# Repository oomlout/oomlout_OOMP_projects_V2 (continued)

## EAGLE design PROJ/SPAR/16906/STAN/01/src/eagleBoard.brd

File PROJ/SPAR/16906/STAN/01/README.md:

Contents
========

* [PRPR16906 > Qwiic Multi Port Board](#prpr16906--qwiic-multi-port-board)
	* [OOMP Parts](#oomp-parts)
	* [Images](#images)
	* [Tags](#tags)
  
![][im]
# PRPR16906 > Qwiic Multi Port Board

- ID: PROJ-SPAR-16906-STAN-01
- Hex ID: PRPR16906
- Name: Qwiic Multi Port Board
- Path: oomlout_OOMP_projects_V2/PROJ/SPAR/16906/STAN/01/
- Description: Qwiic Multi Port Board
- Long Link: [http://oom.lt/PROJ-SPAR-16906-STAN-01](http://oom.lt/PROJ-SPAR-16906-STAN-01)
- Short Link: [http://oom.lt/PRPR16906](http://oom.lt/PRPR16906)

## OOMP Parts

|Image|OOMP ID|Designators|
| :--- | :--- | :--- |
||[HEAD-JSTSH-X-PI04-RS](https://github.com/oomlout/oomlout_OOMP_parts_V2/tree/main/HEAD/JSTSH/X/PI04/RS/)|[J4,J3,J2,J1](https://github.com/oomlout/oomlout_OOMP_parts_V2/tree/main/HEAD/JSTSH/X/PI04/RS/)|
||||

## Images

|kicadPcb3dFront<br>|kicadPcb3dBack<br>|kicadPcb3d<br>|pcbdraw<br>|
| :---: | :---: | :---: | :---: |
|pcbdrawBack<br>||||

## Tags

|Tag Name|Tag Code|Tag Value|
| :--- | :--- | :--- |
|OOMP Type|oompType|PROJ|
|OOMP Size|oompSize|SPAR|
|OOMP Color|oompColor|16906|
|OOMP Description|oompDesc|STAN|
|OOMP Index|oompIndex|01|
|Full OOMP ID|oompID|PROJ-SPAR-16906-STAN-01|
|Hex ID (short code)|hexID|PRPR16906|
|name|name|Qwiic Multi Port Board|
|gitRepo|gitRepo|https://github.com/sparkfun/Qwiic_Multi_Port_Board|
|gitName|gitName|Qwiic_Multi_Port_Board|
|eagleBoard|eagleBoard|/Qwiic_Multi_Port_Board/Qwiic_Multi_Port_Board.brd|
|eagleSchem|eagleSchem|/Qwiic_Multi_Port_Board/Qwiic_Multi_Port_Board.sch|
|OOMP Parts List|oompParts|<table><tr><td>'J4'</td></tr><tr><td> <table><tr><td>'OOMPID'</td></tr><tr><td> 'HEAD-JSTSH-X-PI04-RS'</td><td> 'FULL'</td></tr><tr><td> <table><tr><td>'DESC'</td></tr><tr><td> ''</td><td> 'PART'</td></tr><tr><td> 'J4'</td><td> 'DEVICE'</td></tr><tr><td> 'JST04_1MM_RA QWIIC_RIGHT_ANGLE'</td><td> 'PACKAGE'</td></tr><tr><td> 'JST04_1MM_RA'</td><td> 'PARTLETTER'</td></tr><tr><td> 'J'</td><td> 'VALUE'</td></tr><tr><td> 'QWIIC_RIGHT_ANGLE'</td><td> 'VALUENUMBER'</td></tr><tr><td> '__'</td><td> 'PACKAGENUMBER'</td></tr><tr><td> '041'</td><td> 'BOM'</td></tr><tr><td> ''</td><td> 'OWNER'</td></tr><tr><td> 'SPAR'</td><td> 'FULL'</td></tr><tr><td> 'J4</td><td>QWIIC_RIGHT_ANGLE</td><td>JST04_1MM_RA QWIIC_RIGHT_ANGLE</td><td>JST04_1MM_RA</td><td></td><td></td><td>'</td></tr></table></td></tr></table></td><td> 'J3'</td></tr><tr><td> <table><tr><td>'OOMPID'</td></tr><tr><td> 'HEAD-JSTSH-X-PI04-RS'</td><td> 'FULL'</td></tr><tr><td> <table><tr><td>'DESC'</td></tr><tr><td> ''</td><td> 'PART'</td></tr><tr><td> 'J3'</td><td> 'DEVICE'</td></tr><tr><td> 'JST04_1MM_RA QWIIC_RIGHT_ANGLE'</td><td> 'PACKAGE'</td></tr><tr><td> 'JST04_1MM_RA'</td><td> 'PARTLETTER'</td></tr><tr><td> 'J'</td><td> 'VALUE'</td></tr><tr><td> 'QWIIC_RIGHT_ANGLE'</td><td> 'VALUENUMBER'</td></tr><tr><td> '__'</td><td> 'PACKAGENUMBER'</td></tr><tr><td> '041'</td><td> 'BOM'</td></tr><tr><td> ''</td><td> 'OWNER'</td></tr><tr><td> 'SPAR'</td><td> 'FULL'</td></tr><tr><td> 'J3</td><td>QWIIC_RIGHT_ANGLE</td><td>JST04_1MM_RA QWIIC_RIGHT_ANGLE</td><td>JST04_1MM_RA</td><td></td><td></td><td>'</td></tr></table></td></tr></table></td><td> 'J2'</td></tr><tr><td> <table><tr><td>'OOMPID'</td></tr><tr><td> 'HEAD-JSTSH-X-PI04-RS'</td><td> 'FULL'</td></tr><tr><td> <table><tr><td>'DESC'</td></tr><tr><td> ''</td><td> 'PART'</td></tr><tr><td> 'J2'</td><td> 'DEVICE'</td></tr><tr><td> 'JST04_1MM_RA QWIIC_RIGHT_ANGLE'</td><td> 'PACKAGE'</td></tr><tr><td> 'JST04_1MM_RA'</td><td> 'PARTLETTER'</td></tr><tr><td> 'J'</td><td> 'VALUE'</td></tr><tr><td> 'QWIIC_RIGHT_ANGLE'</td><td> 'VALUENUMBER'</td></tr><tr><td> '__'</td><td> 'PACKAGENUMBER'</td></tr><tr><td> '041'</td><td> 'BOM'</td></tr><tr><td> ''</td><td> 'OWNER'</td></tr><tr><td> 'SPAR'</td><td> 'FULL'</td></tr><tr><td> 'J2</td><td>QWIIC_RIGHT_ANGLE</td><td>JST04_1MM_RA QWIIC_RIGHT_ANGLE</td><td>JST04_1MM_RA</td><td></td><td></td><td>'</td></tr></table></td></tr></table></td><td> 'J1'</td></tr><tr><td> <table><tr><td>'OOMPID'</td></tr><tr><td> 'HEAD-JSTSH-X-PI04-RS'</td><td> 'FULL'</td></tr><tr><td> <table><tr><td>'DESC'</td></tr><tr><td> ''</td><td> 'PART'</td></tr><tr><td> 'J1'</td><td> 'DEVICE'</td></tr><tr><td> 'JST04_1MM_RA QWIIC_RIGHT_ANGLE'</td><td> 'PACKAGE'</td></tr><tr><td> 'JST04_1MM_RA'</td><td> 'PARTLETTER'</td></tr><tr><td> 'J'</td><td> 'VALUE'</td></tr><tr><td> 'QWIIC_RIGHT_ANGLE'</td><td> 'VALUENUMBER'</td></tr><tr><td> '__'</td><td> 'PACKAGENUMBER'</td></tr><tr><td> '041'</td><td> 'BOM'</td></tr><tr><td> ''</td><td> 'OWNER'</td></tr><tr><td> 'SPAR'</td><td> 'FULL'</td></tr><tr><td> 'J1</td><td>QWIIC_RIGHT_ANGLE</td><td>JST04_1MM_RA QWIIC_RIGHT_ANGLE</td><td>JST04_1MM_RA</td><td></td><td></td><td>'</td></tr></table></td></tr></table></td></tr></table>|
|Parts as pulled from a BOM|rawParts|<table><tr><td>'kicadBom'</td></tr><tr><td> [<table><tr><td>'Part'</td></tr><tr><td> 'U$4'</td><td> 'Value'</td></tr><tr><td> ''</td><td> 'Device'</td></tr><tr><td> 'MULTI1 '</td><td> 'Package'</td></tr><tr><td> 'MULTI1'</td><td> 'Description'</td></tr><tr><td> ''</td><td> 'BOM'</td></tr><tr><td> ''</td></tr></table></td><td> <table><tr><td>'Part'</td></tr><tr><td> 'U$7'</td><td> 'Value'</td></tr><tr><td> ''</td><td> 'Device'</td></tr><tr><td> 'MULTI1 '</td><td> 'Package'</td></tr><tr><td> 'MULTI1'</td><td> 'Description'</td></tr><tr><td> ''</td><td> 'BOM'</td></tr><tr><td> ''</td></tr></table></td><td> <table><tr><td>'Part'</td></tr><tr><td> 'J4'</td><td> 'Value'</td></tr><tr><td> 'QWIIC_RIGHT_ANGLE'</td><td> 'Device'</td></tr><tr><td> 'JST04_1MM_RA QWIIC_RIGHT_ANGLE'</td><td> 'Package'</td></tr><tr><td> 'JST04_1MM_RA'</td><td> 'Description'</td></tr><tr><td> ''</td><td> 'BOM'</td></tr><tr><td> ''</td></tr></table></td><td> <table><tr><td>'Part'</td></tr><tr><td> 'J3'</td><td> 'Value'</td></tr><tr><td> 'QWIIC_RIGHT_ANGLE'</td><td> 'Device'</td></tr><tr><td> 'JST04_1MM_RA QWIIC_RIGHT_ANGLE'</td><td> 'Package'</td></tr><tr><td> 'JST04_1MM_RA'</td><td> 'Description'</td></tr><tr><td> ''</td><td> 'BOM'</td></tr><tr><td> ''</td></tr></table></td><td> <table><tr><td>'Part'</td></tr><tr><td> 'J2'</td><td> 'Value'</td></tr><tr><td> 'QWIIC_RIGHT_ANGLE'</td><td> 'Device'</td></tr><tr><td> 'JST04_1MM_RA QWIIC_RIGHT_ANGLE'</td><td> 'Package'</td></tr><tr><td> 'JST04_1MM_RA'</td><td> 'Description'</td></tr><tr><td> ''</td><td> 'BOM'</td></tr><tr><td> ''</td></tr></table></td><td> <table><tr><td>'Part'</td></tr><tr><td> 'J1'</td><td> 'Value'</td></tr><tr><td> 'QWIIC_RIGHT_ANGLE'</td><td> 'Device'</td></tr><tr><td> 'JST04_1MM_RA QWIIC_RIGHT_ANGLE'</td><td> 'Package'</td></tr><tr><td> 'JST04_1MM_RA'</td><td> 'Description'</td></tr><tr><td> ''</td><td> 'BOM'</td></tr><tr><td> ''</td></tr></table></td><td> <table><tr><td>'Part'</td></tr><tr><td> 'FRAME1'</td><td> 'Value'</td></tr><tr><td> 'FRAME-LETTER'</td><td> 'Device'</td></tr><tr><td> 'CREATIVE_COMMONS FRAME-LETTER'</td><td> 'Package'</td></tr><tr><td> 'CREATIVE_COMMONS'</td><td> 'Description'</td></tr><tr><td> ''</td><td> 'BOM'</td></tr><tr><td> ''</td></tr></table></td><td> <table><tr><td>'Part'</td></tr><tr><td> 'H1'</td><td> 'Value'</td></tr><tr><td> 'STAND-OFFTIGHT'</td><td> 'Device'</td></tr><tr><td> 'STAND-OFF-TIGHT STAND-OFFTIGHT'</td><td> 'Package'</td></tr><tr><td> 'STAND-OFF-TIGHT'</td><td> 'Description'</td></tr><tr><td> ''</td><td> 'BOM'</td></tr><tr><td> ''</td></tr></table></td><td> <table><tr><td>'Part'</td></tr><tr><td> 'H2'</td><td> 'Value'</td></tr><tr><td> 'STAND-OFFTIGHT'</td><td> 'Device'</td></tr><tr><td> 'STAND-OFF-TIGHT STAND-OFFTIGHT'</td><td> 'Package'</td></tr><tr><td> 'STAND-OFF-TIGHT'</td><td> 'Description'</td></tr><tr><td> ''</td><td> 'BOM'</td></tr><tr><td> ''</td></tr></table></td><td> <table><tr><td>'Part'</td></tr><tr><td> 'U$5'</td><td> 'Value'</td></tr><tr><td> ''</td><td> 'Device'</td></tr><tr><td> 'PORT2 '</td><td> 'Package'</td></tr><tr><td> 'PORT2'</td><td> 'Description'</td></tr><tr><td> ''</td><td> 'BOM'</td></tr><tr><td> ''</td></tr></table></td><td> <table><tr><td>'Part'</td></tr><tr><td> 'U$8'</td><td> 'Value'</td></tr><tr><td> ''</td><td> 'Device'</td></tr><tr><td> 'PORT2 '</td><td> 'Package'</td></tr><tr><td> 'PORT2'</td><td> 'Description'</td></tr><tr><td> ''</td><td> 'BOM'</td></tr><tr><td> ''</td></tr></table></td><td> <table><tr><td>'Part'</td></tr><tr><td> 'U$1'</td><td> 'Value'</td></tr><tr><td> ''</td><td> 'Device'</td></tr><tr><td> 'QWIIC_6MM '</td><td> 'Package'</td></tr><tr><td> 'QWIIC_6MM'</td><td> 'Description'</td></tr><tr><td> ''</td><td> 'BOM'</td></tr><tr><td> ''</td></tr></table></td><td> <table><tr><td>'Part'</td></tr><tr><td> 'U$3'</td><td> 'Value'</td></tr><tr><td> ''</td><td> 'Device'</td></tr><tr><td> 'QWIIC_6MM '</td><td> 'Package'</td></tr><tr><td> 'QWIIC_6MM'</td><td> 'Description'</td></tr><tr><td> ''</td><td> 'BOM'</td></tr><tr><td> ''</td></tr></table></td><td> <table><tr><td>'Part'</td></tr><tr><td> 'U$2'</td><td> 'Value'</td></tr><tr><td> ''</td><td> 'Device'</td></tr><tr><td> 'SPARKX-SMALL '</td><td> 'Package'</td></tr><tr><td> 'SPARKX-SMALL'</td><td> 'Description'</td></tr><tr><td> ''</td><td> 'BOM'</td></tr><tr><td> ''</td></tr></table>]</td><td> 'eagleBom'</td></tr><tr><td> []</td></tr></table>|
||||

[im]: kicadPcb3d_450.png

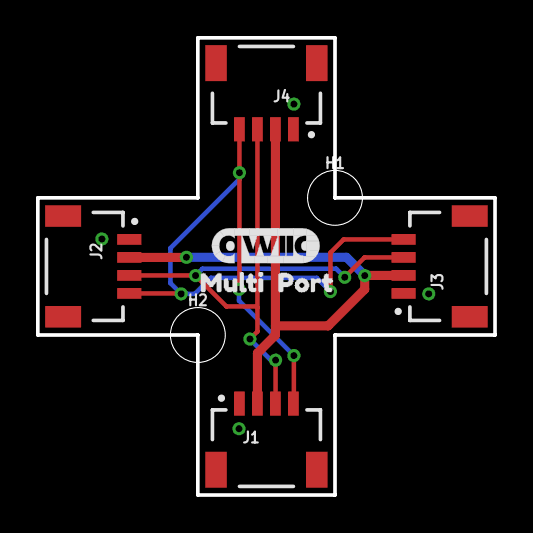
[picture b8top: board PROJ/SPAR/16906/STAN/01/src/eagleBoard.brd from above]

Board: 2 copper layers, 25.4 x 25.4 mm, 14 parts (4 on the bottom side), 4 nets.

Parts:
FRAME1: FRAME-LETTER; CREATIVE_COMMONS
H1, H2: STAND-OFFTIGHT; STAND-OFF-TIGHT
J1, J2, J3, J4: QWIIC_RIGHT_ANGLE; JST04_1MM_RA
U$1, U$3: QWIIC_6MM
U$2: SPARKX-SMALL
U$4, U$7: MULTI1
U$5, U$8: PORT2

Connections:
3.3V: J1.2, J2.2, J3.2, J4.2
GND: J1.1, J2.1, J3.1, J4.1
SCL: J1.4, J2.4, J3.4, J4.4
SDA: J1.3, J2.3, J3.3, J4.3

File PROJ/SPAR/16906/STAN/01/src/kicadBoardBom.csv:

"Id";"Designator";"Package";"Quantity";"Designation";"Supplier and ref";
1;"U$4,U$7";"MULTI1";2;"";;;
2;"J4,J3,J2,J1";"JST04_1MM_RA";4;"QWIIC_RIGHT_ANGLE";;;
3;"FRAME1";"CREATIVE_COMMONS";1;"FRAME-LETTER";;;
4;"H1,H2";"STAND-OFF-TIGHT";2;"STAND-OFFTIGHT";;;
5;"U$5,U$8";"PORT2";2;"";;;
6;"U$1,U$3";"QWIIC_6MM";2;"";;;
7;"U$2";"SPARKX-SMALL";1;"";;;

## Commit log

2022-10-21 Created ADAF and SPAR projects.
2022-10-21 Copied board files.
2022-10-21 Added jsons.
2022-10-21 Images and readmes.
2022-10-22 Images added to readme, resolutions added.
2022-10-24 Csv and readme changes.
2022-10-24 Copied files over.
2022-10-24 Low numbers and iboms
2022-10-24 Moved kicad files.
2022-10-24 Moved some files to src/
2022-10-25 New kicad and resolutions.
2022-10-25 Rreadme update kicad pcb and schematics added.
2022-10-26 Parts from boms in.
2022-10-26 Added parts matching.
2022-10-26 Added semi functional table to tag display.
2022-10-26 Fixed up images?
2022-10-27 Added kicad schematics.
2022-10-28 Added roper OOMPinstances.
2022-10-28 Changed parts.
2022-10-28 OOMP parts list update.
2022-10-28 Changed default voltage on CAPC-0805-X-UF10
2022-10-28 Matched after some new VREG's
2022-10-28 Raw parts test.
2022-10-28 Fixed changing detailspartysRaws.
2022-10-28 Fixing up.
2022-10-28 Json's
2022-10-29 Readme's fixed up.
2022-10-30 Doing a bit.
2022-10-30 Full run fixup.
2022-10-30 Full update.
2022-11-01 Project run through.
2022-11-01 Matched some parts.
2022-11-01 Added projects.
2022-11-02 A couple of extras.
2022-11-03 A few new bits.
2022-11-03 Full parts oomp added.
2022-11-04 Changes.
2022-11-05 More board details.
2022-11-09 Bit of a rebase.
2022-11-10 Regenerated.
2022-11-10 Fixed duplicating parts lists.
2022-11-10 Quickly Adding Everything
2022-11-11 Fixed naming mistake.
2022-11-14 Project update.
2022-11-14 Readme fixup.
2022-11-15 Readme changes.
